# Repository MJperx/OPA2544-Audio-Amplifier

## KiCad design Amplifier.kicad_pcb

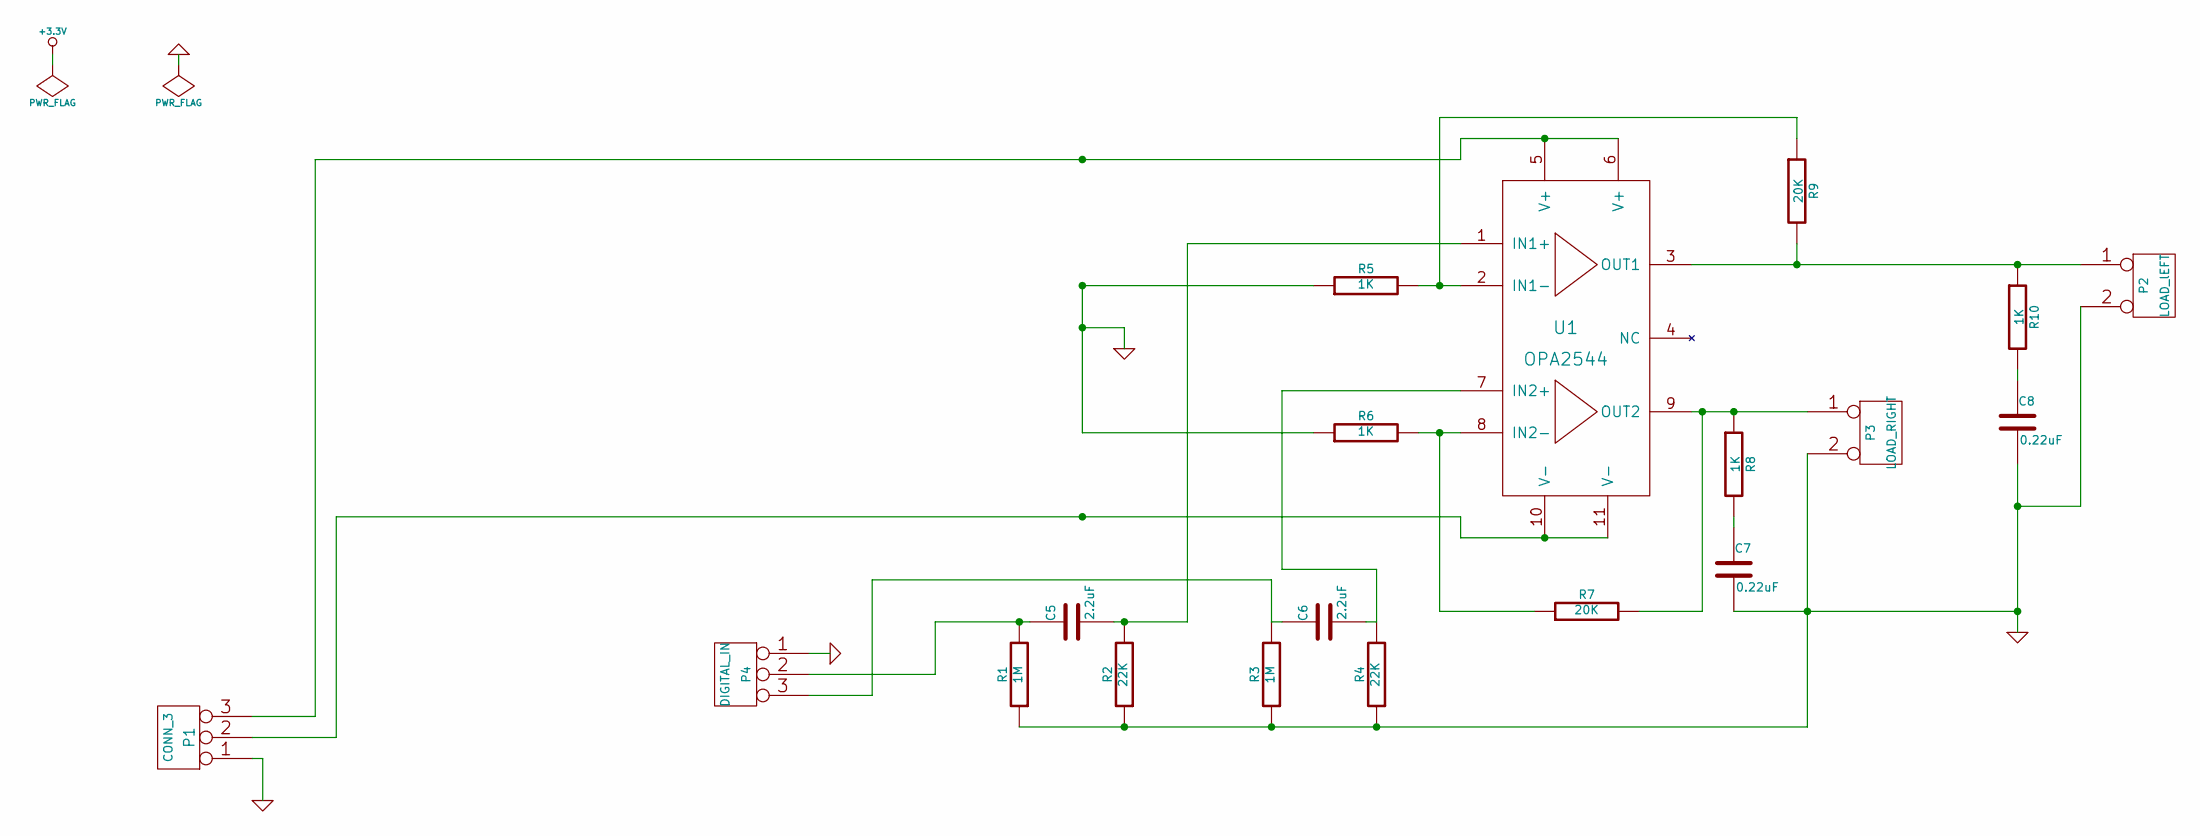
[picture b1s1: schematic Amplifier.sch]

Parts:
C5, C6: 2.2uF
C7, C8: 0.22uF
P1: CONN_3
P2: LOAD_lEFT
P3: LOAD_RIGHT
P4: DIGITAL_IN
R1, R3: 1M
R2, R4: 22K
R5, R6, R8, R10: 1K
R7, R9: 20K
U1: OPA2544

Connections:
GND: C7.2, C8.2, P1.1, P2.2 (PM), P3.2 (PM), P4.1, R1.1, R2.1, R3.1, R4.1, R5.1, R6.1
unnamed: C6.2, R4.2, U1.7 (IN2+)
unnamed: R5.2, R9.1, U1.2 (IN1-)
unnamed: R6.2, R7.1, U1.8 (IN2-)
unnamed: C6.1, P4.3, R3.2
unnamed: C7.1, R8.2
unnamed: P2.1, R9.2, R10.1, U1.3 (OUT1)
unnamed: C8.1, R10.2
unnamed: P3.1, R7.2, R8.1, U1.9 (OUT2)
unnamed: P1.3, U1.5 (V+), U1.6 (V+)
unnamed: P1.2 (PM), U1.10 (V-), U1.11 (V-)
unnamed: C5.1, P4.2 (PM), R1.2
unnamed: C5.2, R2.2, U1.1 (IN1+)

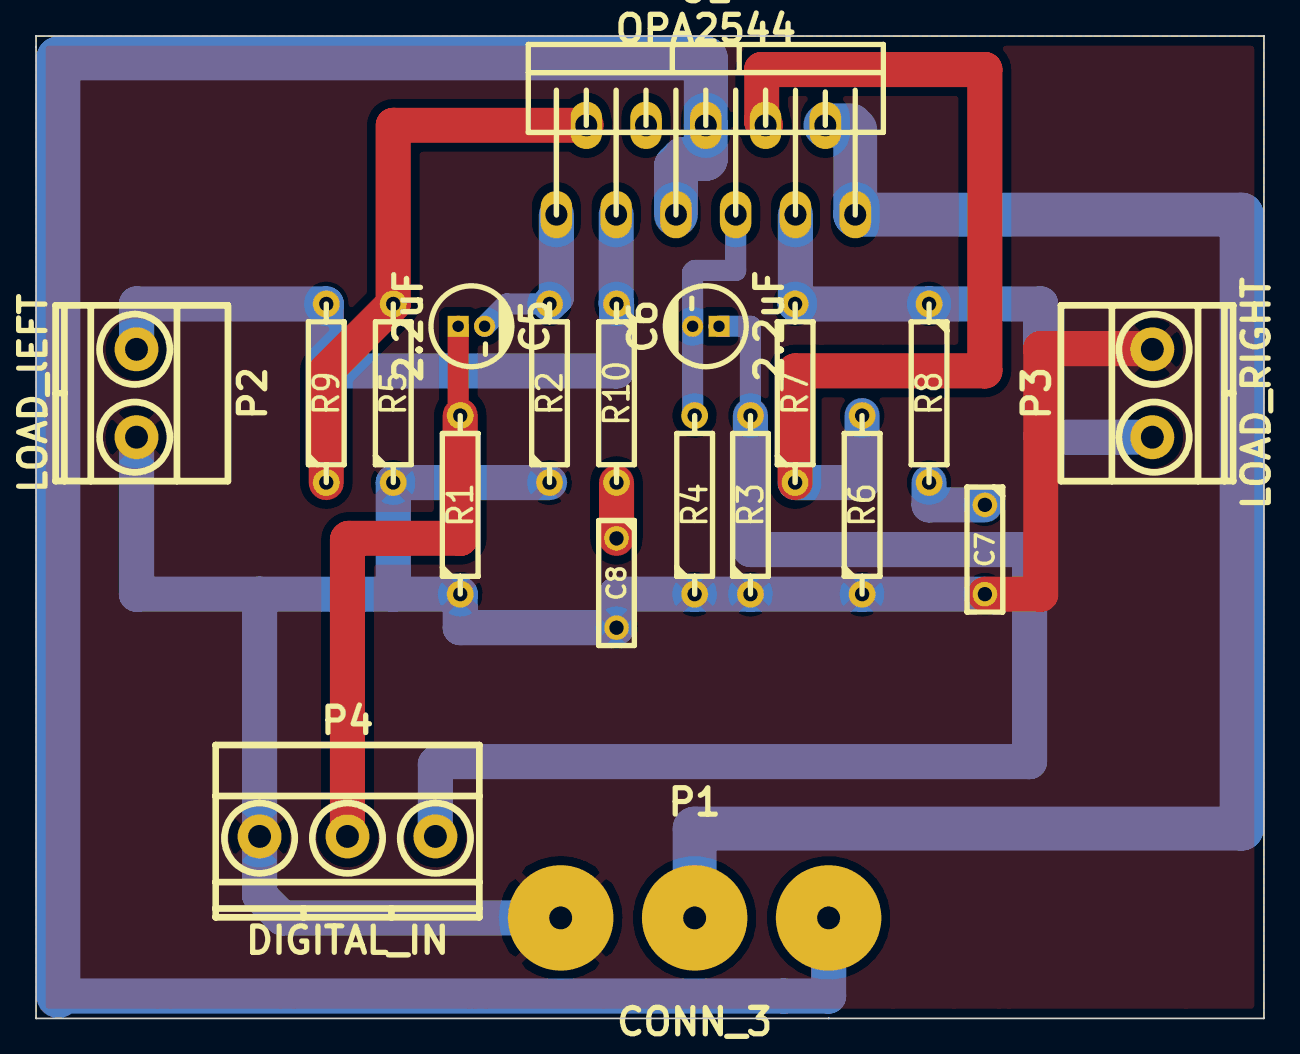
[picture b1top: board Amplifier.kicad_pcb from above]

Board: 2 copper layers, 69.8 x 55.9 mm, 19 parts (0 on the bottom side), 13 nets.

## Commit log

2017-03-15 First commit.
